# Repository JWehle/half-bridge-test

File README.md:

# half-bridge-test
A test board for a half bridge driver circuit with custom features.

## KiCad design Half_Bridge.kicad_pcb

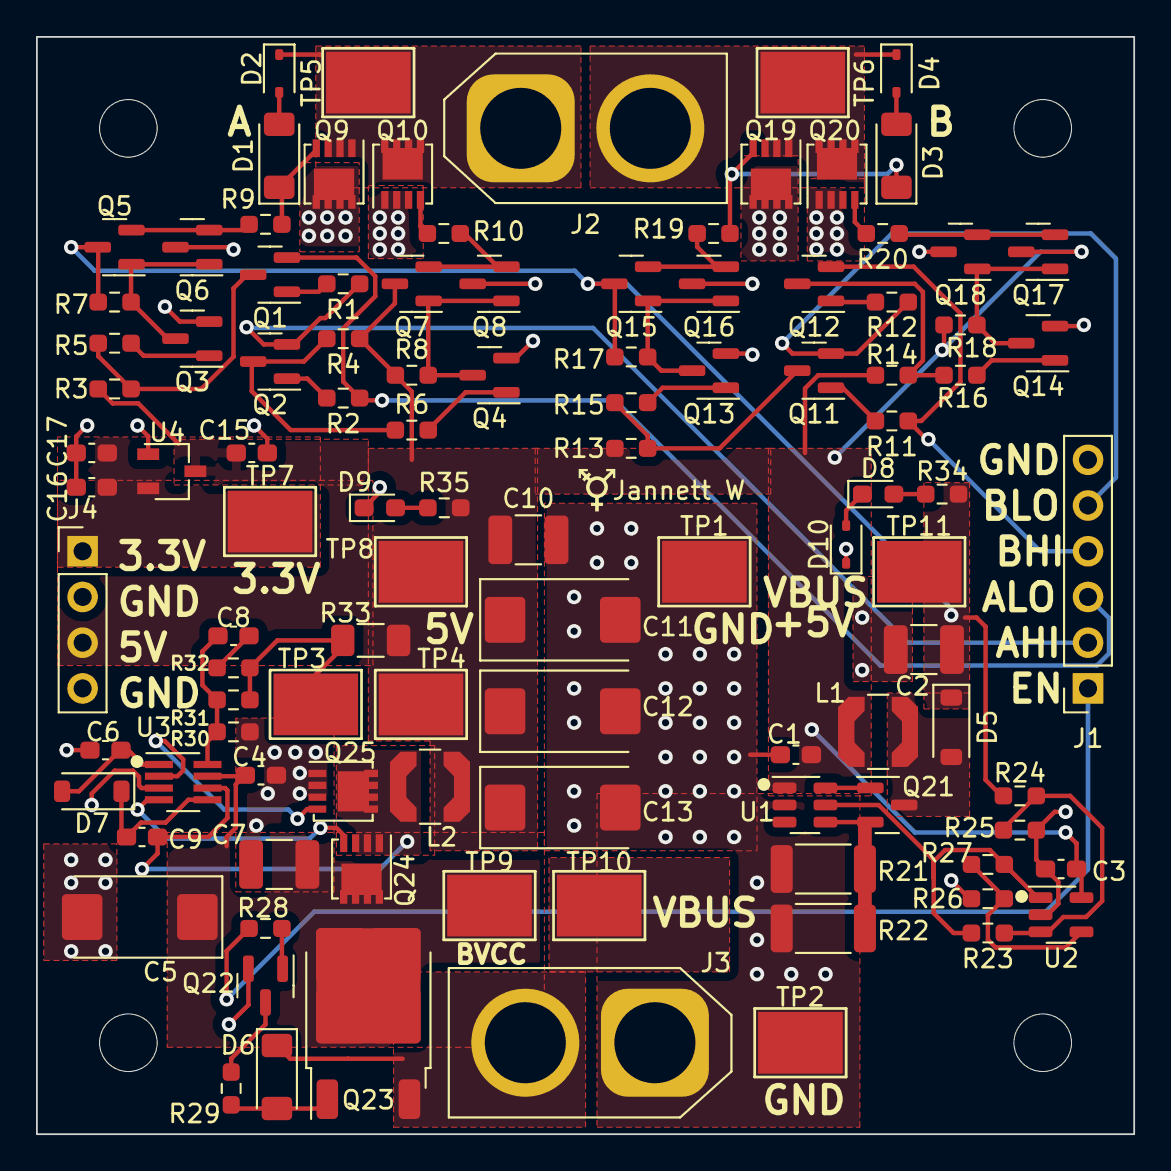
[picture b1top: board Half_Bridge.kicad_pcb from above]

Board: 4 copper layers, 61.0 x 61.0 mm, 113 parts (1 on the bottom side), 59 nets.

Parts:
C1, C6, C17: 2.2uF; C_0603_1608Metric_Pad1.08x0.95mm_HandSolder
C2, C7, C10: 22uF; C_1210_3225Metric_Pad1.33x2.70mm_HandSolder
C3, C4, C9, C15, C16: 0.1uF; C_0603_1608Metric_Pad1.08x0.95mm_HandSolder
C5: 47uF; CP_EIA-7343-43_Kemet-X_Pad2.25x2.55mm_HandSolder
C8: 20pF; C_0603_1608Metric_Pad1.08x0.95mm_HandSolder
C11, C12, C13: 68uF; CP_EIA-7343-43_Kemet-X_Pad2.25x2.55mm_HandSolder
D1, D3, D6: BZV55B10; D_MiniMELF
D2, D4, D10: 1N4148WS; D_SOD-323
D5, D7: MBR0540; D_SOD-123
D8, D9: LED; LED_0603_1608Metric_Pad1.05x0.95mm_HandSolder
H1, H2, H3, H4: MountingHole; MountingHole_3.2mm_M3
J1: Conn_01x06; PinSocket_1x06_P2.54mm_Vertical
J2: XT60-M; AMASS_XT60-M_1x02_P7.20mm_Vertical
J3: XT60-F; AMASS_XT60-F_1x02_P7.20mm_Vertical
J4: Conn_01x04; PinHeader_1x04_P2.54mm_Vertical
L1, L2: 4.7uH; L_Coilcraft_LPS4018
Q1, Q2, Q3, Q4, Q5, Q7, Q11, Q12, Q13, Q14, Q15, Q17, Q21, Q22: MMBT3904; SOT-23
Q6, Q8, Q16, Q18: MMBT3906; SOT-23
Q9, Q10, Q19, Q20, Q24, Q25: SiS176LDN; Vishay_PowerPAK_1212-8_Single
Q23: QM6015D; TO-252-2
R1, R2, R3, R4, R5, R6, R7, R8, R11, R12, R13, R14, R15, R16, R17, R18, R28, R29: 10k; R_0603_1608Metric_Pad0.98x0.95mm_HandSolder
R9, R19, R34, R35: 1k; R_0603_1608Metric_Pad0.98x0.95mm_HandSolder
R10, R20: 100; R_0603_1608Metric_Pad0.98x0.95mm_HandSolder
R21, R22: 0.39; R_2010_5025Metric
R23: 0; R_0603_1608Metric_Pad0.98x0.95mm_HandSolder
R24, R26: 12k; R_0603_1608Metric_Pad0.98x0.95mm_HandSolder
R25, R27: 3k; R_0603_1608Metric_Pad0.98x0.95mm_HandSolder
R30: 15k; R_0603_1608Metric_Pad0.98x0.95mm_HandSolder
R31: 47k; R_0603_1608Metric_Pad0.98x0.95mm_HandSolder
R32: 20k; R_0603_1608Metric_Pad0.98x0.95mm_HandSolder
R33: 20; R_1206_3216Metric_Pad1.30x1.75mm_HandSolder
SYMBOL1, SYMBOL2: Trans_Symbol
TP1, TP2, TP3, TP4, TP5, TP6, TP7, TP8, TP9, TP10, TP11: 5016; TestPoint_Keystone_5016_Compact
U1: ZXSC420E6TA; SOT-23-6
U2: OPA344NA/250; SOT-23-5
U3: RT8110BGJ8; SOT-23-8_Handsoldering
U4: AP2138N-3.3TRG1; TSOT-23

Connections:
+3.3V: C16.1, C17.1, J4.1, TP7.1, U4.2 (VO)
+5.5V: C6.1, D7.2 (A), U3.1 (VCC)
+5V: C1.1, C3.1, C10.1, C11.1, C12.1, C13.1, C15.1, J4.3, L1.1, L2.2, Q7.3 (C), Q17.3 (C), R3.1, R4.1, R8.1, R13.1, R14.1, R18.1, R33.2, R35.1, TP4.1, TP8.1, U1.1 (VCC), U2.5 (V+), U4.3 (VI)
/BOOST_FB: R23.2, R27.2, U1.5 (VFB), U2.1
/BOOST_SW: D5.2 (A), L1.2, Q21.3 (C)
/BUCK_FB: C8.1, R30.1, R31.1, U3.8 (FB)
/BUCK_SW: C9.2, L2.1, Q24.1 (S), Q24.2 (S), Q24.3 (S), Q25.5 (D), U3.6 (PHASE)
/BUCK_VCC: C4.1, C5.1, C7.1, Q23.2 (D), Q24.5 (D), TP9.1, U3.7 (VIN)
GND: C1.2, C2.2, C3.2, C4.2, C5.2, C6.2, C7.2, C10.2, C11.2, C12.2, C13.2, C15.2, C16.2, C17.2, D9.1 (K), J1.6, J3.1, J4.2, J4.4, Q3.2 (E), Q4.2 (E), Q6.3 (C), Q8.3 (C), Q10.1 (S), Q10.2 (S), Q10.3 (S), Q13.2 (E), Q14.2 (E), Q16.3 (C), Q18.3 (C), Q20.1 (S), Q20.2 (S), Q20.3 (S), Q22.2 (E), Q25.1 (S), Q25.2 (S), Q25.3 (S), R21.1, R22.1, R25.2, R30.2, TP1.1, TP2.1, U1.2 (GND), U2.2 (V-), U3.3 (GND), U4.1 (GND)
HI_LOGIC_A: J1.2, Q2.2 (E), R1.1
HI_LOGIC_B: J1.4, Q12.2 (E), R11.1
LO_LOGIC_A: J1.3, Q1.2 (E), R2.1
LO_LOGIC_B: J1.5, Q11.2 (E), R12.1
unnamed: C8.2, R32.1
unnamed: D1.2 (A), D2.2 (A)
unnamed: D1.1 (K), Q9.4 (G), R9.2
unnamed: D3.2 (A), D4.2 (A)
unnamed: D3.1 (K), Q19.4 (G), R19.2
unnamed: D6.2 (A), Q23.1 (G), R29.1
unnamed: C9.1, D7.1 (K), U3.5 (BOOT)
unnamed: D8.2 (A), R34.2
unnamed: D9.2 (A), R35.2
unnamed: D8.1 (K), D10.2 (A)
unnamed: Q1.1 (B), R1.2
unnamed: Q1.3 (C), R3.2, R5.1
unnamed: Q2.1 (B), R2.2
unnamed: Q2.3 (C), R4.2, R6.1
unnamed: Q3.1 (B), R5.2
unnamed: Q3.3 (C), Q5.1 (B), Q6.1 (B), R7.2
unnamed: Q4.1 (B), R6.2
unnamed: Q4.3 (C), Q7.1 (B), Q8.1 (B), R8.2
unnamed: Q5.2 (E), Q6.2 (E), R9.1
unnamed: Q7.2 (E), Q8.2 (E), R10.1
unnamed: Q10.4 (G), R10.2
unnamed: Q11.1 (B), R11.2
unnamed: Q11.3 (C), R13.2, R15.1
unnamed: Q12.1 (B), R12.2
unnamed: Q12.3 (C), R14.2, R16.1
unnamed: Q13.1 (B), R15.2
unnamed: Q13.3 (C), Q15.1 (B), Q16.1 (B), R17.2
unnamed: Q14.1 (B), R16.2
unnamed: Q14.3 (C), Q17.1 (B), Q18.1 (B), R18.2
unnamed: Q15.2 (E), Q16.2 (E), R19.1
unnamed: Q17.2 (E), Q18.2 (E), R20.1
unnamed: Q20.4 (G), R20.2
unnamed: Q21.1 (B), U1.6 (V_DRIVE)
unnamed: Q21.2 (E), R21.2, R22.2, U1.4 (I_SENSE)
unnamed: Q22.1 (B), R28.1
unnamed: Q22.3 (C), R29.2
unnamed: Q24.4 (G), U3.4 (UGATE)
unnamed: Q25.4 (G), U3.2 (LGATE)
unnamed: R31.2, R32.2, R33.1, TP3.1
unnamed: R23.1, R24.2, R25.1, U2.3 (+)
unnamed: R26.2, R27.1, U2.4 (-)
OUT_A: D2.1 (K), J2.1, Q9.1 (S), Q9.2 (S), Q9.3 (S), Q10.5 (D), TP5.1
OUT_B: D4.1 (K), J2.2, Q19.1 (S), Q19.2 (S), Q19.3 (S), Q20.5 (D), TP6.1
PWR_ENABLE: J1.1, R28.2
VBUS: D6.1 (K), D10.1 (K), J3.2, Q9.5 (D), Q19.5 (D), Q23.3 (S), R26.1, TP10.1
VBUS+5V: C2.1, D5.1 (K), Q5.3 (C), Q15.3 (C), R7.1, R17.1, R24.1, R34.1, TP11.1
